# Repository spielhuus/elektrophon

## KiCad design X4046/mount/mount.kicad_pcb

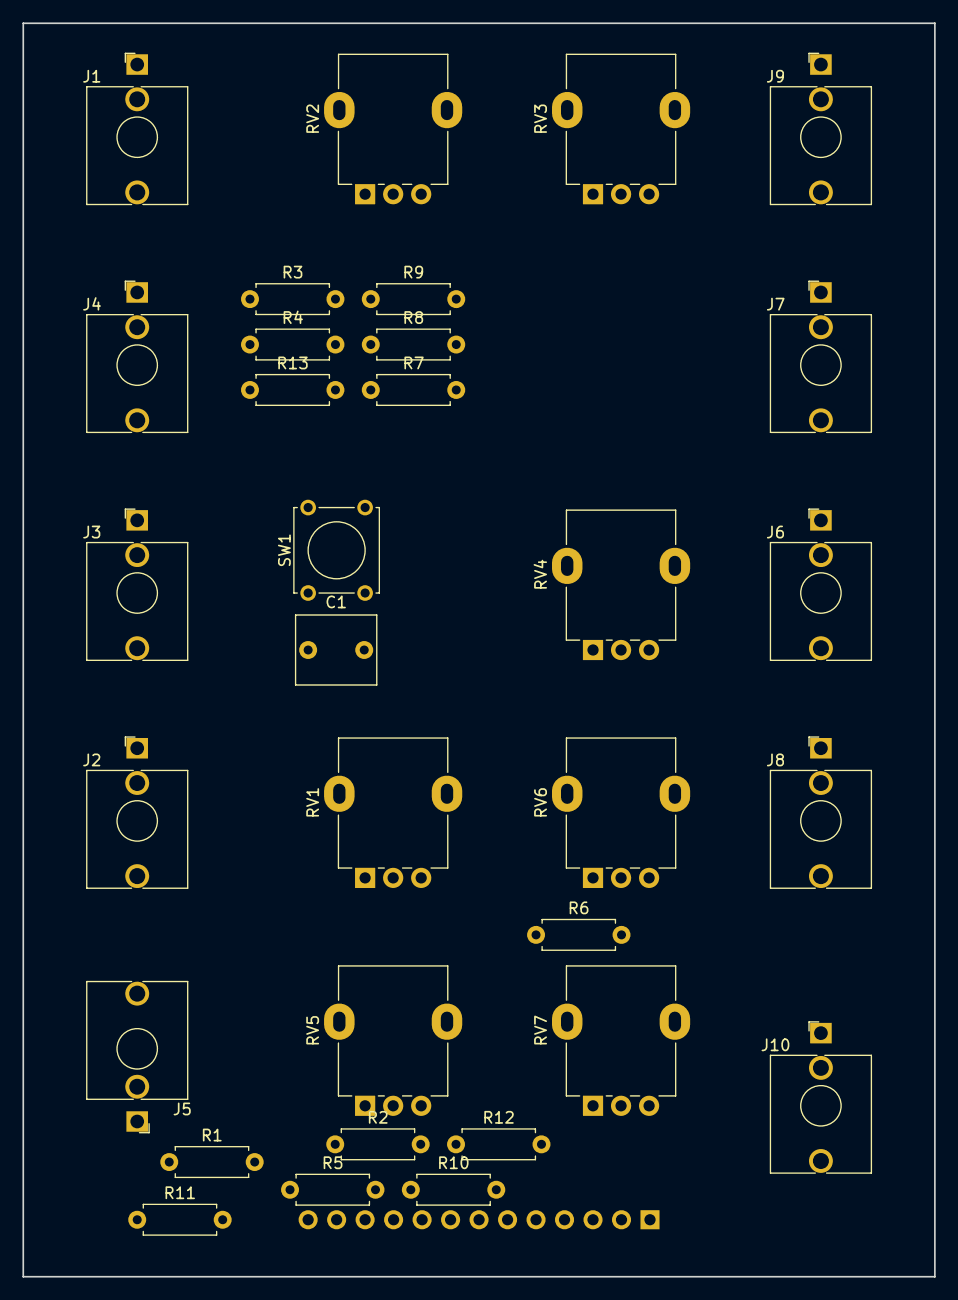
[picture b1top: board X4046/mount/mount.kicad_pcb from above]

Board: 2 copper layers, 81.3 x 111.8 mm, 33 parts (1 on the bottom side), 29 nets, no tracks yet.

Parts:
C1: 0.22u; C_Rect_L7.0mm_W6.0mm_P5.00mm
J1, J2, J3, J4, J5, J6, J7, J8, J9, J10: AudioJack2_SwitchT; Jack_3.5mm_QingPu_WQP-PJ398SM_Vertical_CircularHoles
J11: Conn_01x13_Male; PinHeader_1x13_P2.54mm_Vertical
R1, R2, R3, R5, R6: 100k; R_Axial_DIN0207_L6.3mm_D2.5mm_P7.62mm_Horizontal
R4: 3M3; R_Axial_DIN0207_L6.3mm_D2.5mm_P7.62mm_Horizontal
R7: 330k; R_Axial_DIN0207_L6.3mm_D2.5mm_P7.62mm_Horizontal
R8, R9, R12, R13: 1k; R_Axial_DIN0207_L6.3mm_D2.5mm_P7.62mm_Horizontal
R10: 3k; R_Axial_DIN0207_L6.3mm_D2.5mm_P7.62mm_Horizontal
R11: 1k8; R_Axial_DIN0207_L6.3mm_D2.5mm_P7.62mm_Horizontal
RV1, RV2, RV3, RV4, RV5: 100k; Potentiometer_Alpha_RD901F-40-00D_Single_Vertical
RV6, RV7: 500k; Potentiometer_Alpha_RD901F-40-00D_Single_Vertical
SW1: SW_SPST; SW_Tactile_Straight_KSL0Axx1LFTR

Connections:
+15V: J11.11, RV2.1, RV3.1, RV7.1
-15V: J11.12, RV2.3, RV3.3, RV7.3
/EXP_FM: J11.1, R1.1, R2.1, R3.1, R4.1
/HARD_SYNC: J4.T, J11.3
/LIN_FM: J11.2, R5.1
/PULSE: J11.10, R10.2, R11.2
/PWM: J11.5, R6.1, R7.1
/RAMPOID: J11.8, R9.1
/SAW: J11.9, R13.1, RV6.3
/SINE: J11.6, R8.1
/SKEW: J11.4, RV6.2
/TRIANGLE: J11.7, R12.1, RV6.1
GND: J1.S, J2.S, J3.S, J4.S, J5.S, J6.S, J7.S, J8.S, J9.S, J10.S, J11.13, R11.1, RV1.3, RV4.3, RV5.3
unnamed: C1.1, J3.T, SW1.1
unnamed: C1.2, RV4.1, SW1.2
unnamed: J1.T, R1.2
unnamed: J2.T, RV1.1
unnamed: J5.T, RV5.1
unnamed: J6.T, R8.2
unnamed: J7.T, R12.2
unnamed: J8.T, R9.2
unnamed: J9.T, R13.2
unnamed: J10.T, R10.1
unnamed: R2.2, RV1.2
unnamed: R3.2, RV2.2
unnamed: R4.2, RV3.2
unnamed: R5.2, RV4.2
unnamed: R6.2, RV5.2
unnamed: R7.2, RV7.2

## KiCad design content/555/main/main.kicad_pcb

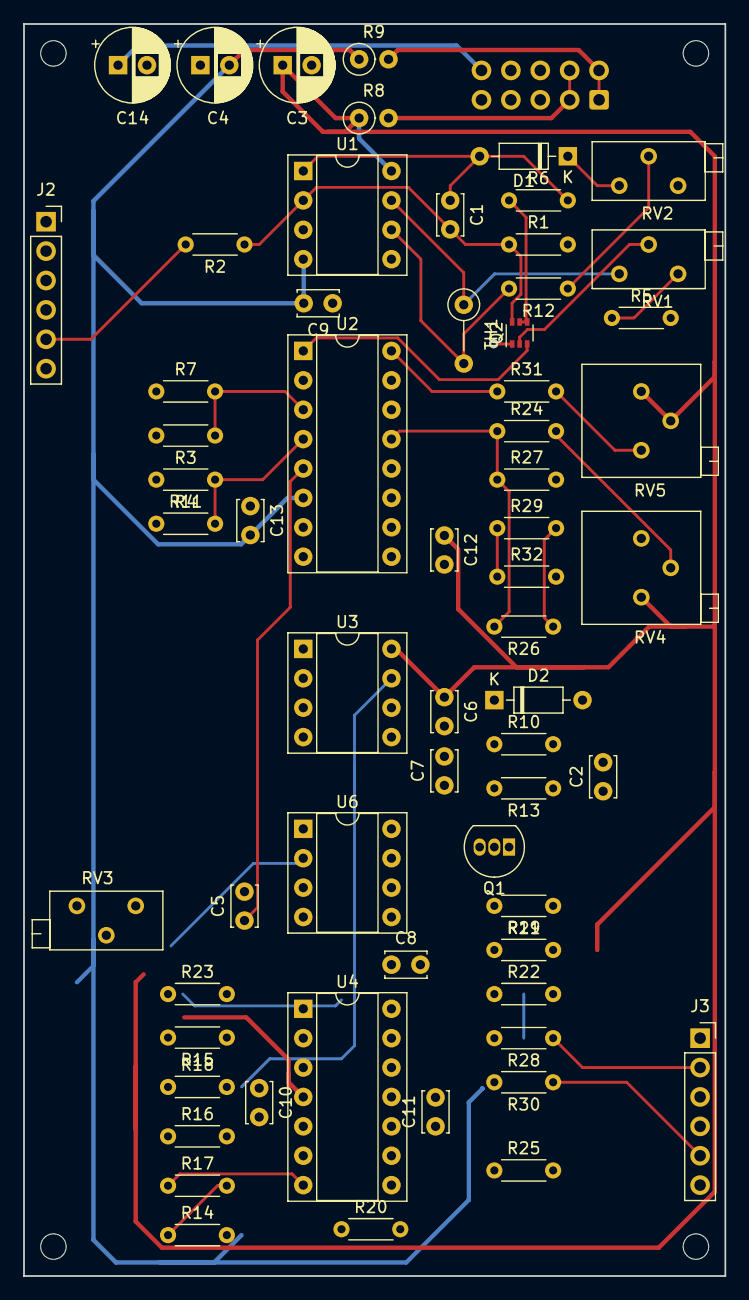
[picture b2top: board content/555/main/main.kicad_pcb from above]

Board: 2 copper layers, 60.6 x 108.2 mm, 68 parts (1 on the bottom side), 45 nets.

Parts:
C1: 100p; C_Disc_D3.4mm_W2.1mm_P2.50mm
C2: 470p; C_Disc_D3.4mm_W2.1mm_P2.50mm
C3, C4, C14: 22u; CP_Radial_D6.3mm_P2.50mm
C5: 2200p; C_Disc_D3.4mm_W2.1mm_P2.50mm
C6, C8, C9, C10, C11, C12, C13: 0.1u; C_Disc_D3.4mm_W2.1mm_P2.50mm
C7: 0.001u; C_Disc_D3.4mm_W2.1mm_P2.50mm
D1, D2: 1N4148; D_DO-35_SOD27_P7.62mm_Horizontal
H1, H2, H3, H4: MountingHole; MountingHole_2.2mm_M2
J1: IDC Header; IDC-Header_2x05_P2.54mm_Vertical
J2, J3: Conn_01x06_Female; PinSocket_1x06_P2.54mm_Vertical
Q1: BC550; TO-92_Inline
Q2: PMP5201; SOT-363_SC-70-6
R1: 1M5; R_Axial_DIN0204_L3.6mm_D1.6mm_P5.08mm_Horizontal
R2, R12, R16, R24: 1M; R_Axial_DIN0204_L3.6mm_D1.6mm_P5.08mm_Horizontal
R3, R13: 4k7; R_Axial_DIN0204_L3.6mm_D1.6mm_P5.08mm_Horizontal
R4, R7: 1k5; R_Axial_DIN0204_L3.6mm_D1.6mm_P5.08mm_Horizontal
R5, R27: 390; R_Axial_DIN0204_L3.6mm_D1.6mm_P5.08mm_Horizontal
R6: 22k; R_Axial_DIN0204_L3.6mm_D1.6mm_P5.08mm_Horizontal
R8, R9: 10; R_Axial_DIN0207_L6.3mm_D2.5mm_P2.54mm_Vertical
R10, R15, R17, R26: 100k; R_Axial_DIN0204_L3.6mm_D1.6mm_P5.08mm_Horizontal
R11, R18, R19, R20, R23: 10k; R_Axial_DIN0204_L3.6mm_D1.6mm_P5.08mm_Horizontal
R14: 150k; R_Axial_DIN0204_L3.6mm_D1.6mm_P5.08mm_Horizontal
R21, R22: 20k; R_Axial_DIN0204_L3.6mm_D1.6mm_P5.08mm_Horizontal
R25: 120k; R_Axial_DIN0204_L3.6mm_D1.6mm_P5.08mm_Horizontal
R28: 2k2; R_Axial_DIN0204_L3.6mm_D1.6mm_P5.08mm_Horizontal
R29, R31: 39k; R_Axial_DIN0204_L3.6mm_D1.6mm_P5.08mm_Horizontal
R30: 2M2; R_Axial_DIN0204_L3.6mm_D1.6mm_P5.08mm_Horizontal
R32: 300k; R_Axial_DIN0204_L3.6mm_D1.6mm_P5.08mm_Horizontal
RV1: 100; Potentiometer_Bourns_3296Z_Horizontal
RV2, RV3: 100k; Potentiometer_Bourns_3296Z_Horizontal
RV4: 100k; Potentiometer_Bourns_3296P_Horizontal
RV5: 25k; Potentiometer_Bourns_3296P_Horizontal
TH1: 2k +3500ppm/°C; R_Axial_DIN0207_L6.3mm_D2.5mm_P5.08mm_Vertical
U1, U6: TL072; DIP-8_W7.62mm_Socket
U2: LM13700; DIP-16_W7.62mm_Socket
U3: TLC555xP; DIP-8_W7.62mm_Socket
U4: TL074; DIP-14_W7.62mm_Socket

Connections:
+5V: C14.1, J1.9, J1.10, J2.1
+15V: C3.1, C6.1, C8.1, C10.1, C12.1, J2.4, R8.1, R11.1, R13.1, R19.2, RV3.1, RV4.1, RV5.2, RV5.3, U1.8, U2.11, U3.8, U4.4
-15V: C4.2, C9.2, C11.2, C13.2, J2.3, R1.2, R9.1, R14.2, RV3.3, RV4.3, U1.4, U2.6, U4.11
/exp_fm: J2.6, R12.2, TH1.2, U1.6
/lin_fm: J2.5, R2.2
/net_q: R3.2, U3.3
/pulse: J3.5, R30.1, U4.14
/pwm_cv: J3.6, R25.2, U4.9
/ramp: J3.4, R23.1, U4.1
/sine: J3.3, U2.9
/sync: C2.2, J3.1
/triangle: J3.2, R22.1, R26.1, R28.1, R29.2, U6.7
GND: C3.2, C4.1, C5.2, C6.2, C7.2, C8.2, C9.1, C10.2, C11.1, C12.2, C13.1, C14.2, D2.2, J1.5, J1.6, J1.7, J1.8, J2.2, Q1.3, Q2.1, R4.2, R5.2, R7.1, R21.1, R27.2, R32.2, RV2.3, U1.3, U1.5, U2.14, U3.1, U4.5, U4.10
unnamed: C1.1, D1.2, R6.2, U1.1
unnamed: C1.2, Q2.6, R1.1, R2.1, U1.2
unnamed: C2.1, R10.2
unnamed: C5.1, U2.5, U6.3
unnamed: C7.1, U3.5
unnamed: D1.1, RV2.1
unnamed: D2.1, Q1.2, R10.1
unnamed: Q1.1, R13.2, U3.4
unnamed: Q2.2, RV1.2
unnamed: Q2.3, U2.1
unnamed: Q2.4, Q2.5, R6.1
unnamed: R3.1, R7.2, U2.3
unnamed: R5.1, RV1.3
unnamed: R4.1, R11.2, U2.4
unnamed: R12.1, RV2.2
unnamed: R14.1, R15.1, R16.2, R17.2, U4.6
unnamed: R15.2, U3.2, U3.6, U6.1, U6.2, U6.5
unnamed: R16.1, RV3.2
unnamed: R17.1, R18.1, R20.1, U4.7
unnamed: R18.2, U3.7, U4.3
unnamed: R19.1, R21.2, R22.2, U6.6
unnamed: R20.2, R23.2, U4.2
unnamed: R24.1, R26.2, R27.1, U2.13
unnamed: R24.2, RV4.2
unnamed: R25.1, U4.8, U4.13
unnamed: R28.2, R30.2, U4.12
unnamed: R29.1, R32.1, U2.10, U2.12
unnamed: R31.1, U2.16
unnamed: R31.2, RV5.1
unnamed: RV1.1, TH1.1, U1.7
VN: J1.1, J1.2, R9.2
VP: J1.3, J1.4, R8.2

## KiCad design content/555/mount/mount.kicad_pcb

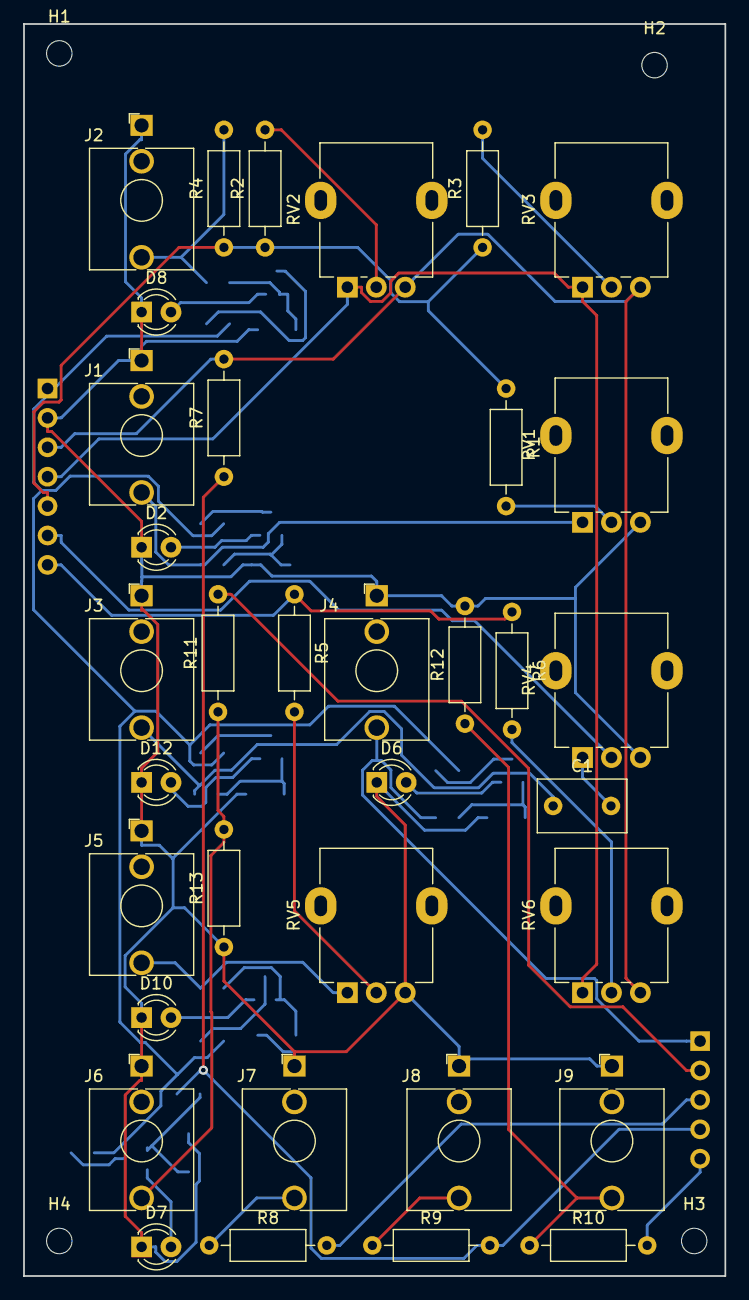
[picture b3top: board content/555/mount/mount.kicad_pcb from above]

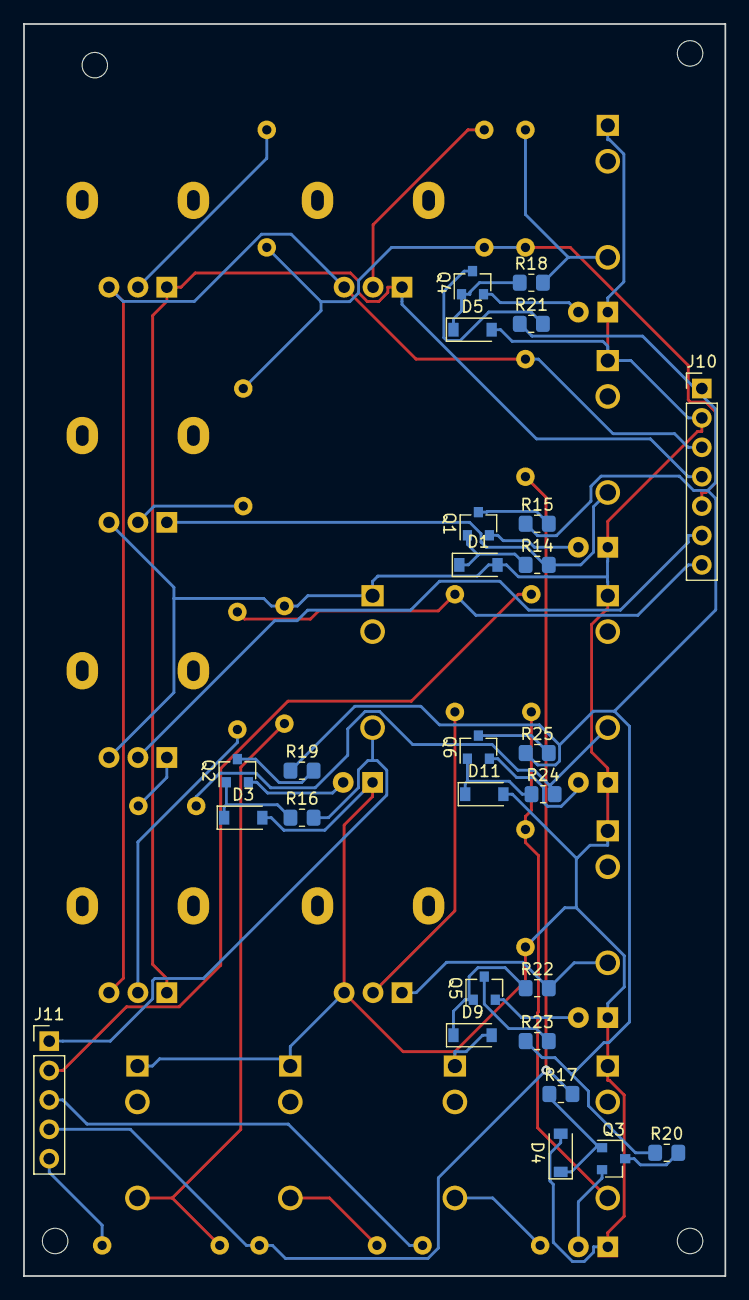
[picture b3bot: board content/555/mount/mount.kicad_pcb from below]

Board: 2 copper layers, 60.6 x 108.2 mm, 65 parts (26 on the bottom side), 44 nets.

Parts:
C1: 0.22u; C_Disc_D7.5mm_W4.4mm_P5.00mm
D1, D3, D4, D5, D9, D11: 1N4148W; D_SOD-123
D2, D6, D7, D8, D10, D12: LED; LED_D3.0mm
H1, H2, H3, H4: MountingHole; MountingHole_2.2mm_M2
J1: exp.fm; Jack_3.5mm_WQP-PJ398SM_Vertical
J2: 1v/oct; Jack_3.5mm_WQP-PJ398SM_Vertical
J3: lin.fm; Jack_3.5mm_WQP-PJ398SM_Vertical
J4: sync; Jack_3.5mm_WQP-PJ398SM_Vertical
J5: pwm; Jack_3.5mm_WQP-PJ398SM_Vertical
J6, J7, J8, J9: AudioJack2_SwitchT; Jack_3.5mm_WQP-PJ398SM_Vertical
J10: Conn_01x07_Male; PinHeader_1x07_P2.54mm_Vertical
J11: Conn_01x05_Male; PinHeader_1x05_P2.54mm_Vertical
Q1, Q2, Q3, Q4, Q5, Q6: MMBT3904; SOT-23
R1, R2, R4, R5: 100k; R_Axial_DIN0207_L6.3mm_D2.5mm_P10.16mm_Horizontal
R3: 3M3; R_Axial_DIN0207_L6.3mm_D2.5mm_P10.16mm_Horizontal
R6: 330k; R_Axial_DIN0207_L6.3mm_D2.5mm_P10.16mm_Horizontal
R7: 5k6; R_Axial_DIN0207_L6.3mm_D2.5mm_P10.16mm_Horizontal
R8, R9: 1k; R_Axial_DIN0207_L6.3mm_D2.5mm_P10.16mm_Horizontal
R10: 3k; R_Axial_DIN0207_L6.3mm_D2.5mm_P10.16mm_Horizontal
R11, R13: 2k; R_Axial_DIN0207_L6.3mm_D2.5mm_P10.16mm_Horizontal
R12: 1k8; R_Axial_DIN0207_L6.3mm_D2.5mm_P10.16mm_Horizontal
R14, R16, R17, R18, R22, R24: 100k; R_0805_2012Metric_Pad1.20x1.40mm_HandSolder
R15, R21, R25: 5.1k; R_0805_2012Metric_Pad1.20x1.40mm_HandSolder
R19, R20, R23: 5k; R_0805_2012Metric_Pad1.20x1.40mm_HandSolder
RV1, RV2, RV3, RV4, RV5, RV6: 100k; Potentiometer_Alpha_RD901F-40-00D_Single_Vertical

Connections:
+5V: J10.1, R15.1, R19.1, R20.1, R21.1, R23.1, R25.1
+15V: J10.4, RV2.1, RV3.1, RV6.1
-15V: J10.3, R7.2, RV2.3, RV3.3, RV6.3
/exp.fm: J1.T, R14.2, RV1.1
/exp_fm: J10.5, R1.1, R2.1, R3.1, R4.1
/lin.fm: C1.1, J3.T, R24.2
/lin_fm: J10.6, RV4.2
/pulse: J11.5, R10.2
/pwm: J5.T, R22.2, RV5.1
/pwm_cv: J10.7, R5.1, R6.1
/ramp: J11.3, R8.2
/sine: J11.4, R7.1, R9.2, R17.2
/sync: J4.T, J11.1, R16.2
/triangle: J11.2, R11.2
/v_oct: J2.T, R4.2, R18.2
GND: D1.2, D2.1, D3.2, D4.2, D5.2, D6.1, D7.1, D8.1, D9.2, D10.1, D11.2, D12.1, J1.S, J2.S, J3.S, J4.S, J5.S, J6.S, J7.S, J8.S, J9.S, J10.2, R12.2, R13.1, RV1.3, RV4.3, RV5.3
unnamed: C1.2, RV4.1
unnamed: D1.1, Q1.1, R14.1
unnamed: D2.2, Q1.2
unnamed: D3.1, Q2.1, R16.1
unnamed: D4.1, Q3.1, R17.1
unnamed: D5.1, Q4.1, R18.1
unnamed: D6.2, Q2.2
unnamed: D7.2, Q3.2
unnamed: D8.2, Q4.2
unnamed: D9.1, Q5.1, R22.1
unnamed: D10.2, Q5.2
unnamed: D11.1, Q6.1, R24.1
unnamed: D12.2, Q6.2
unnamed: J6.T, R11.1, R13.2
unnamed: J7.T, R8.1
unnamed: J8.T, R9.1
unnamed: J9.T, R10.1, R12.1
unnamed: Q1.3, R15.2
unnamed: Q2.3, R19.2
unnamed: Q3.3, R20.2
unnamed: Q4.3, R21.2
unnamed: Q5.3, R23.2
unnamed: Q6.3, R25.2
unnamed: R1.2, RV1.2
unnamed: R2.2, RV2.2
unnamed: R3.2, RV3.2
unnamed: R5.2, RV5.2
unnamed: R6.2, RV6.2

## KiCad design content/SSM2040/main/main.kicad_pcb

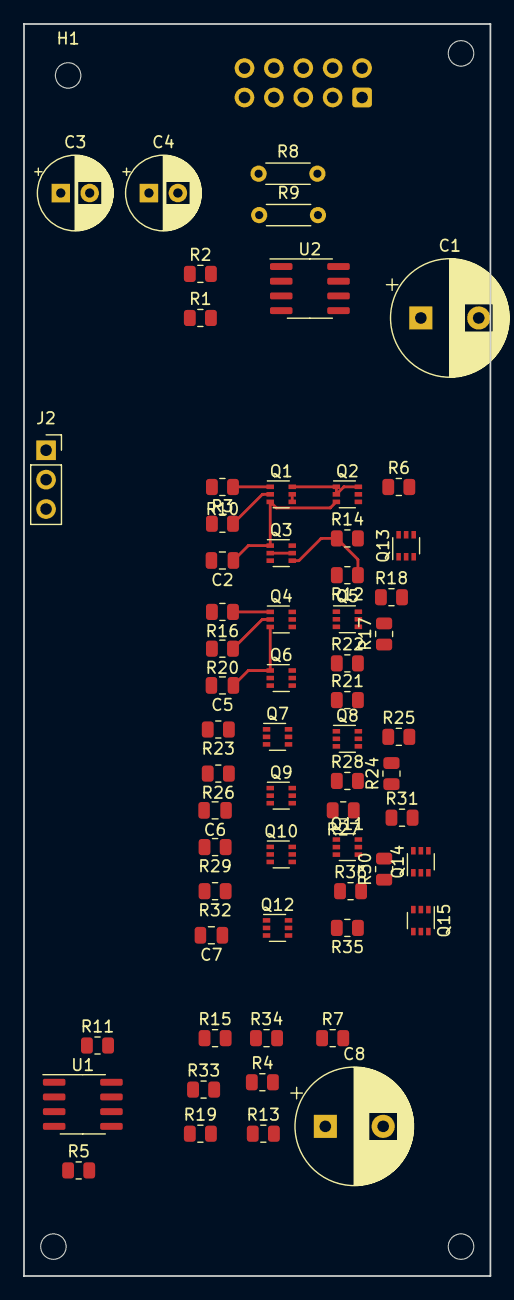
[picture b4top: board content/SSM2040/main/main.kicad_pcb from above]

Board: 2 copper layers, 40.3 x 108.2 mm, 67 parts (1 on the bottom side), 50 nets.

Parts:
C1, C8: 10u; CP_Radial_D10.0mm_P5.00mm
C2, C5, C6, C7: 1n; C_0805_2012Metric
C3, C4: 22u; CP_Radial_D6.3mm_P2.50mm
H1, H2, H3, H4: MountingHole; MountingHole_2.2mm_M2
J1: 10 Pos; IDC-Header_2x05_P2.54mm_Vertical
J2: Conn_01x03_Female; PinSocket_1x03_P2.54mm_Vertical
Q1, Q3, Q4, Q6, Q7, Q9, Q10, Q12, Q13, Q14, Q15: DMMT3904W; SOT-363_SC-70-6
Q2, Q5, Q8, Q11: DMMT3906W; SOT-363_SC-70-6
R1, R2, R12, R14, R17, R21, R22, R24, R27, R28, R30, R33, R35, R36: 10k; R_0805_2012Metric
R3, R10, R16, R20, R23, R26, R29, R32: 220; R_0805_2012Metric
R4, R34: 100k; R_0805_2012Metric
R5: 200k; R_0805_2012Metric
R6, R13, R18, R25, R31: 1k; R_0805_2012Metric
R7: 51k; R_0805_2012Metric
R8, R9: 10; R_Axial_DIN0204_L3.6mm_D1.6mm_P5.08mm_Horizontal
R11: 27k; R_0805_2012Metric
R15: 1M; R_0805_2012Metric
R19: 2.2k; R_0805_2012Metric
U1, U2: TL072; SOIC-8_3.9x4.9mm_P1.27mm

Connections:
+5V: C2.2, C5.2, C6.2, C7.2, J1.9, J1.10, R3.2, R10.2, R16.2, R20.2, R23.2, R26.2, R29.2, R32.2
+15V: C3.1, Q2.4, Q2.5, Q3.3, Q3.6, Q5.4, Q5.5, Q6.3, Q6.6, Q8.4, Q8.5, Q9.3, Q9.6, Q11.4, Q11.5, Q12.3, Q12.6, R8.1, R15.1, U1.8, U2.8
-15V: C4.2, R5.2, R9.1, R14.2, R22.2, R28.2, R36.2, U1.4, U2.4
/CV: J2.2, R4.2
/IN: J2.1, R1.2
/OUT: J2.3, R34.1, U2.1
GND: C3.2, C4.1, J1.5, J1.6, J1.7, J1.8, Q13.1, Q13.2, Q14.1, Q14.2, R13.2, U1.3, U1.5, U2.3
unnamed: C1.1, R1.1, R2.1
unnamed: C1.2, Q1.2, R10.1, R12.2
unnamed: C2.1, Q1.3, Q2.3, Q3.1
unnamed: C5.1, Q4.3, Q5.3, Q6.1
unnamed: C6.1, Q7.3, Q8.3, Q9.1
unnamed: C7.1, Q10.3, Q11.3, Q12.1
unnamed: C8.1, Q12.4, R35.1, R36.1
unnamed: C8.2, R33.1
unnamed: Q1.1, R3.1
unnamed: Q1.4, Q1.5, R6.1
unnamed: Q1.6, Q2.1, Q2.2, Q2.6
unnamed: Q3.2, Q3.5
unnamed: Q3.4, R12.1, R14.1, R17.2
unnamed: Q4.1, R16.1
unnamed: Q4.2, R17.1, R20.1, R21.2
unnamed: Q4.4, Q4.5, R18.1
unnamed: Q4.6, Q5.1, Q5.2, Q5.6
unnamed: Q6.2, Q6.5
unnamed: Q6.4, R21.1, R22.1, R24.2
unnamed: Q7.1, R23.1
unnamed: Q7.2, R24.1, R26.1, R27.2
unnamed: Q7.4, Q7.5, R25.1
unnamed: Q7.6, Q8.1, Q8.2, Q8.6
unnamed: Q9.2, Q9.5
unnamed: Q9.4, R27.1, R28.1, R30.2
unnamed: Q10.1, R29.1
unnamed: Q10.2, R30.1, R32.1, R35.2
unnamed: Q10.4, Q10.5, R31.1
unnamed: Q10.6, Q11.1, Q11.2, Q11.6
unnamed: Q12.2, Q12.5
unnamed: Q13.3, R18.2
unnamed: Q13.4, Q13.5, Q14.4, Q14.5, Q15.5, R19.1
unnamed: Q13.6, R6.2
unnamed: Q14.3, R25.2
unnamed: Q14.6, R31.2
unnamed: Q15.1, R11.1, R13.1
unnamed: Q15.6, R15.2, U1.6
unnamed: R4.1, R5.1, R7.2, U1.2
unnamed: R7.1, R11.2, U1.1
unnamed: R19.2, U1.7
unnamed: R33.2, R34.2, U2.2
VN: J1.1, J1.2, R9.2
VP: J1.3, J1.4, R8.2

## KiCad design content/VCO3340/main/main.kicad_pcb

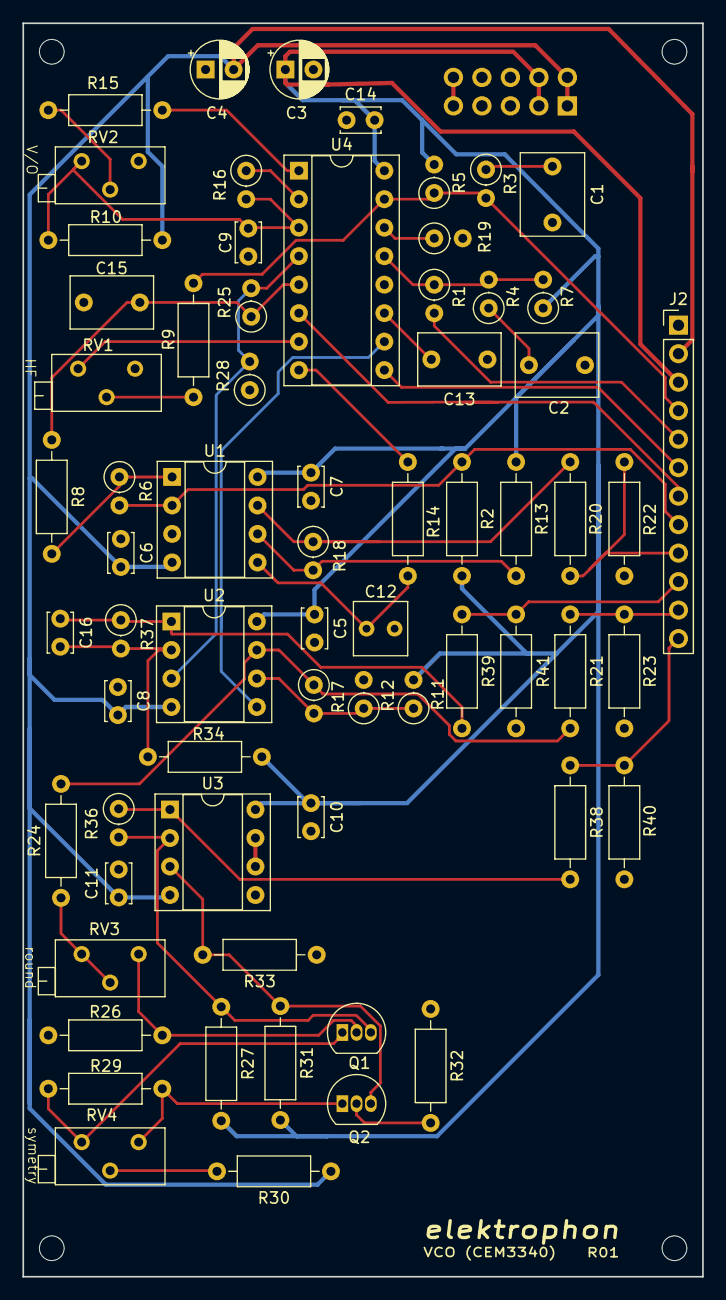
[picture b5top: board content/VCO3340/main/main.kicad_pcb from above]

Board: 2 copper layers, 60.6 x 111.8 mm, 72 parts (1 on the bottom side), 46 nets.

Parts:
C1, C2: 0.01u; C_Rect_L7.2mm_W5.5mm_P5.00mm_FKS2_FKP2_MKS2_MKP2
C3, C4: 10u; CP_Radial_D5.0mm_P2.50mm
C5, C6, C7, C8, C9, C10, C11, C14: 0.1u; C_Disc_D3.4mm_W2.1mm_P2.50mm
C12: 33p; C_Rect_L4.6mm_W4.6mm_P2.50mm_MKS02_FKP02
C13: 1000p; C_Rect_L7.2mm_W4.5mm_P5.00mm_FKS2_FKP2_MKS2_MKP2
C15: 0.001u; C_Rect_L7.2mm_W4.5mm_P5.00mm_FKS2_FKP2_MKS2_MKP2
C16: 22p; C_Disc_D3.4mm_W2.1mm_P2.50mm
H1, H2, H3, H4: MountingHole; MountingHole_2.2mm_M2
J1: IDC Header; IDC-Header_2x05_P2.54mm_Vertical
J2: Conn_01x12_Female; PinHeader_1x12_P2.54mm_Vertical
Q1, Q2: 2N3904; TO-92_Inline
R1, R25: 1M; R_Axial_DIN0207_L6.3mm_D2.5mm_P2.54mm_Vertical
R2: 10M; R_Axial_DIN0207_L6.3mm_D2.5mm_P10.16mm_Horizontal
R3, R4: 470; R_Axial_DIN0207_L6.3mm_D2.5mm_P2.54mm_Vertical
R5: 360k; R_Axial_DIN0207_L6.3mm_D2.5mm_P2.54mm_Vertical
R6: 120k; R_Axial_DIN0207_L6.3mm_D2.5mm_P2.54mm_Vertical
R7: 1M5; R_Axial_DIN0207_L6.3mm_D2.5mm_P2.54mm_Vertical
R8, R14, R27, R31: 10k; R_Axial_DIN0207_L6.3mm_D2.5mm_P10.16mm_Horizontal
R9: 1M; R_Axial_DIN0207_L6.3mm_D2.5mm_P10.16mm_Horizontal
R10: 820k; R_Axial_DIN0207_L6.3mm_D2.5mm_P10.16mm_Horizontal
R11: 30k; R_Axial_DIN0207_L6.3mm_D2.5mm_P2.54mm_Vertical
R12, R18, R28: 10k; R_Axial_DIN0207_L6.3mm_D2.5mm_P2.54mm_Vertical
R13, R33: 20k; R_Axial_DIN0207_L6.3mm_D2.5mm_P10.16mm_Horizontal
R15: 24k; R_Axial_DIN0207_L6.3mm_D2.5mm_P10.16mm_Horizontal
R16: 5k6; R_Axial_DIN0207_L6.3mm_D2.5mm_P2.54mm_Vertical
R17: 15k; R_Axial_DIN0207_L6.3mm_D2.5mm_P2.54mm_Vertical
R19: 1k8; R_Axial_DIN0207_L6.3mm_D2.5mm_P2.54mm_Vertical
R20, R21, R41: 1k5; R_Axial_DIN0207_L6.3mm_D2.5mm_P10.16mm_Horizontal
R22, R23: 3k; R_Axial_DIN0207_L6.3mm_D2.5mm_P10.16mm_Horizontal
R24: 47k; R_Axial_DIN0207_L6.3mm_D2.5mm_P10.16mm_Horizontal
R26, R32: 2k2; R_Axial_DIN0207_L6.3mm_D2.5mm_P10.16mm_Horizontal
R29: 390; R_Axial_DIN0207_L6.3mm_D2.5mm_P10.16mm_Horizontal
R30: 18k; R_Axial_DIN0207_L6.3mm_D2.5mm_P10.16mm_Horizontal
R34: 40k; R_Axial_DIN0207_L6.3mm_D2.5mm_P10.16mm_Horizontal
R36: 20k; R_Axial_DIN0207_L6.3mm_D2.5mm_P2.54mm_Vertical
R37: 33k; R_Axial_DIN0207_L6.3mm_D2.5mm_P2.54mm_Vertical
R38, R40: 2k; R_Axial_DIN0207_L6.3mm_D2.5mm_P10.16mm_Horizontal
R39: 2k26; R_Axial_DIN0207_L6.3mm_D2.5mm_P10.16mm_Horizontal
RV1, RV2: 10k; Potentiometer_Bourns_3296Z_Horizontal
RV3, RV4: 50k; Potentiometer_Bourns_3296Z_Horizontal
U1, U2, U3: TL072; DIP-8_W7.62mm_Socket
U4: CEM3340; DIP-16_W7.62mm_Socket

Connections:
+5V: J1.9, J1.10
+15V: C3.1, C5.1, C7.1, C10.1, C14.2, J1.3, J1.4, J2.3, R2.1, R5.2, R7.1, R11.2, R13.2, R27.2, R31.2, R34.2, U1.8, U2.8, U3.8, U4.16
-15V: C4.2, C6.2, C8.2, C11.2, J1.1, J1.2, J2.2, R10.2, R30.1, U1.4, U2.4, U3.4
/CV: J2.4, R3.2, R5.1, R9.1, U4.15
/HARD_SYNC: J2.7, U4.6
/HF_Trim: RV1.3, U4.7
/IN_LIN_FM: J2.5, R1.2
/IN_PWM: J2.8, R2.2, R6.2, U1.2
/LIN_FM: R1.1, R4.2, R7.2, U4.13
/PULSE: J2.10, R39.1, R41.2
/PULSE_RAW: R25.2, R28.2, U2.3, U4.4
/PWM: C15.2, R8.1, R25.1, U4.5
/SAW: J2.9, R20.1, R22.2
/SAW_RAW: R14.2, U4.8
/SINE: J2.12, R38.1, R40.2
/SOFT_SYNC: J2.6, U4.9
/TRIANGLE: J2.11, R21.1, R23.2
/TRI_RAW: U2.5, U4.10
GND: C1.2, C2.2, C3.2, C4.1, C5.2, C6.1, C7.2, C8.1, C9.2, C10.2, C11.1, C12.2, C13.2, C14.1, C15.1, J1.5, J1.6, J1.7, J1.8, J2.1, R12.2, R19.2, R22.1, R23.1, R26.1, R28.1, R32.1, R33.1, R40.1, R41.1, RV1.1, U1.3, U3.5, U4.12
unnamed: C1.1, R3.1
unnamed: C2.1, R4.1
unnamed: C9.1, R10.1, R16.2, RV2.3, U4.3
unnamed: C12.1, R14.1, U1.5
unnamed: C13.1, U4.11
unnamed: C16.1, R37.1, R39.2, U2.1
unnamed: C16.2, R34.1, R37.2, U2.2
unnamed: Q1.1, R29.2, RV4.3
unnamed: Q1.2, R26.2, RV3.1
unnamed: Q1.3, R27.1, R36.2, U3.2
unnamed: Q2.1, R29.1, RV4.1
unnamed: Q2.2, R32.2
unnamed: Q2.3, R31.1, R33.2, U3.3
unnamed: R6.1, R8.2, U1.1
unnamed: R9.2, RV1.2
unnamed: R11.1, R12.1, R17.2, U2.6
unnamed: R13.1, R18.2, U1.6
unnamed: R15.1, U4.1
unnamed: R15.2, RV2.2
unnamed: R16.1, U4.2
unnamed: R17.1, R21.2, R24.2, U2.7
unnamed: R18.1, R20.2, U1.7
unnamed: R19.1, U4.14
unnamed: R24.1, RV3.2, RV3.3
unnamed: R30.2, RV4.2
unnamed: R36.1, R38.2, U3.1
unnamed: U3.6, U3.7

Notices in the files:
content/555/main/main.kicad_pcb:
License CC BY 4.0 - Attribution 4.0 International
